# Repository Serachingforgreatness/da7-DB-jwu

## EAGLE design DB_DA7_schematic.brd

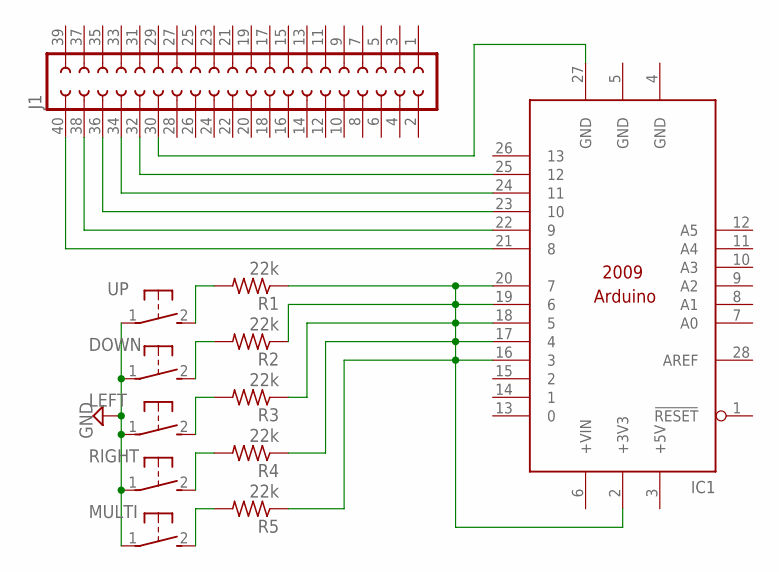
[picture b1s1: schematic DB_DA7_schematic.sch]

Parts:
DOWN: 31-XX; B3F-31XX
IC1: ARDUINO2009_10; ARDUINO2009
J1: SOCKET-40V; S40V
LEFT: 31-XX; B3F-31XX
MULTI: 31-XX; B3F-31XX
R1, R2, R3, R4, R5: 22k; 0204/7
RIGHT: 31-XX; B3F-31XX
UP: 31-XX; B3F-31XX

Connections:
+5V: IC1.3 (+5V)
GND: DOWN.1, IC1.4 (GND), IC1.5 (GND), LEFT.1, MULTI.1, RIGHT.1, UP.1
unnamed: IC1.21 (8), J1.40
unnamed: IC1.22 (9), J1.38
unnamed: IC1.23 (10), J1.36
unnamed: IC1.24 (11), J1.34
unnamed: IC1.25 (12), J1.32
unnamed: IC1.27 (GND), J1.30
unnamed: R1.2, UP.2 (S)
unnamed: DOWN.2 (S), R2.2
unnamed: LEFT.2 (S), R3.2
unnamed: R4.2, RIGHT.2 (S)
unnamed: MULTI.2 (S), R5.2
unnamed: IC1.2 (+3V3), IC1.16 (3), IC1.17 (4), IC1.18 (5), IC1.19 (6), IC1.20 (7), R1.1, R2.1, R3.1, R4.1, R5.1

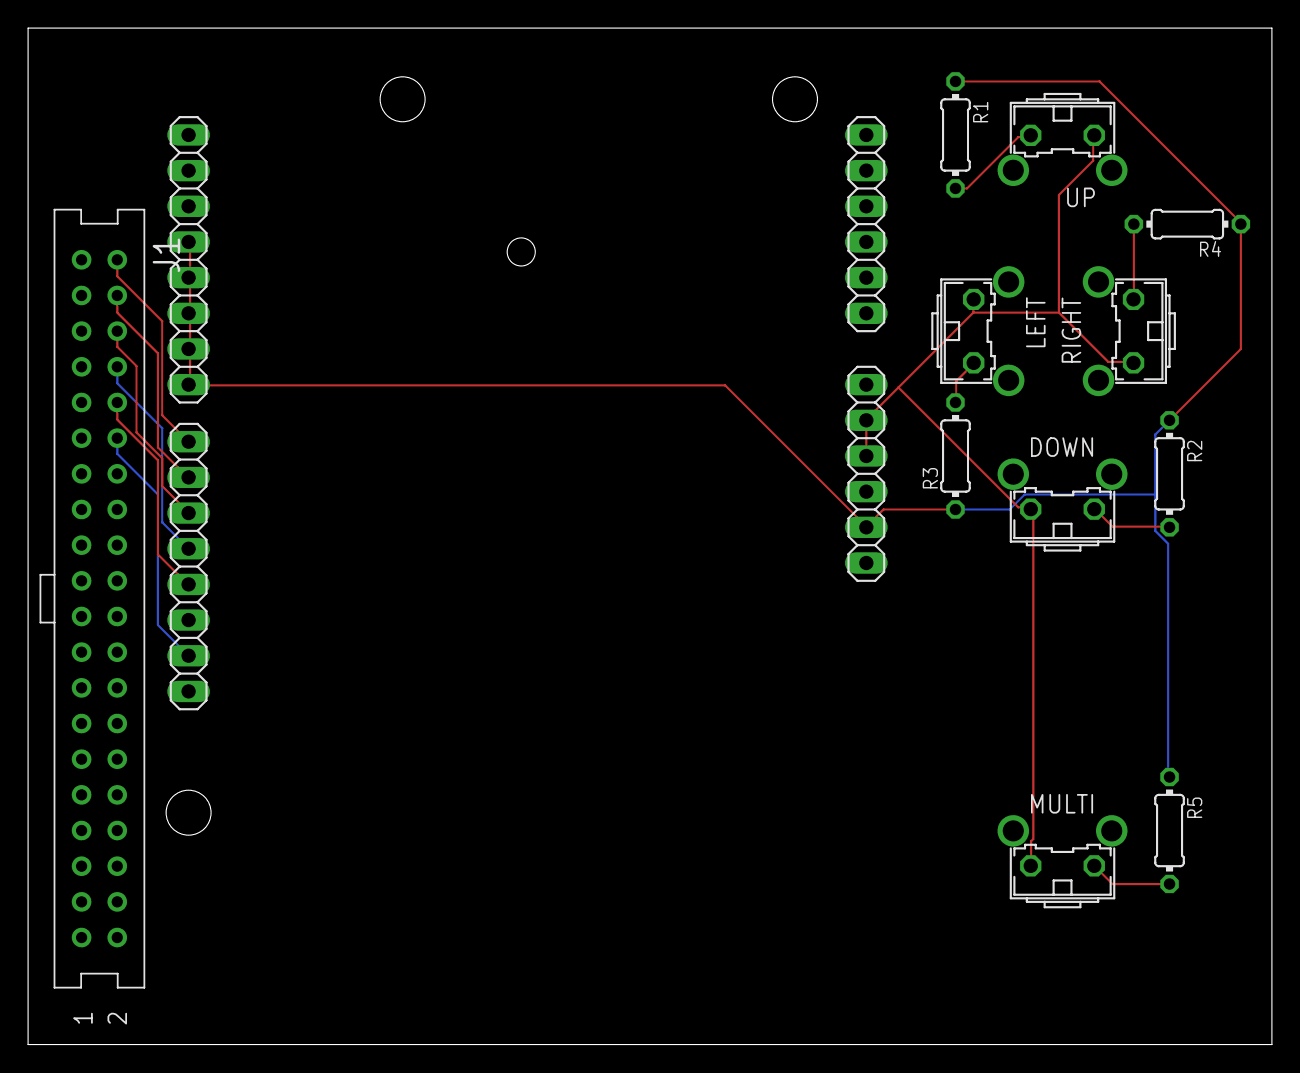
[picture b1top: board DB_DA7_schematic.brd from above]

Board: 2 copper layers, 88.6 x 72.4 mm, 12 parts (0 on the bottom side), 13 nets.
